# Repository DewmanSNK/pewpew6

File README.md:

# pewpew6
## Re-map and Rapid Fire
### Introduction

Based on buffi's original openpewpew, pewpew6 is an Arduino Nano based device for rapid fire and button remap in a JAMMA arcade cabinet. Pewpew6 supports up to 6 input buttons and can map those to any of 6 outputs. It simply connects in-line between the control panel buttons and the existing wiring harness. In an unconfigured state pewpew6 will provide simple passthrough, making it as though pewpew6 was not even installed. To load custom rapid fire and button remapping, pewpew6 leverages NFC cards. An NFC card card be configured with a desired auto fire and button remapping configuration. When the card is in proximity of the NFC reader, PewPew6 will change configuration on the fly and apply the rapid fire and remap settings stored on the card. This allows you to preconfigure you favorite buttons mappings and/or auto fire rates and store those on any number of NFC cards. 

### pewpew6 Features

- 6 button input and 6 outputs
- Button Remap
- Separate frames_on and frames_off rapid fire settings
- NFC card reader for loading settings
- 6 LED indicators show per button configuration

### NFC Card Format

Settings are stored in a 'Text Record' on the NFC card. 

Each line consists of the following comma separated values:  
(Button)(rapid enable)(frames_on)(frames_off)(Output)  

-Only one button definition per line  
-Last button definition ends with ';'  

Line Example
-------
A,0,1,1,1 = Button A, No auto fire enabled, 1 frame_on, 1 frame_off, Output 1  
**Note - When auto fire is disabled, the frame_on/frame_off vales are meaningless**  

Example Text Record 1:
--------------------
A,0,1,1,1  
B,0,1,1,2  
C,0,1,1,3  
D,0,1,1,4  
E,0,1,1,5  
F,0,1,1,6;  

The example text record 1 shown above displays the correct format. The settings in this example are the default settings stored in the Arduino.   
No rapid fire, no remapping - passthrough only.  

Example Text Record 2:
--------------------
A,0,1,1,1  
B,1,2,2,1  
C,1,1,4,1  
D,1,4,4,1  
E,1,10,1,1  
F,1,5,5,1;  

The example text record 2 shown above maps all 6 buttons to JAMMA-1  
Button A has no rapid fire, 1 frame_on, 1 frame_off, JAMMA-1  
Button B has rapid fire enabled, 1 frame_on, 1 frame_off, JAMMA-1  
Button C has rapid fire enabled, 1 frame_on, 4 frame_off, JAMMA-1  
Button D has rapid fire enabled, 4 frame_on, 4 frame_off, JAMMA-1  
Button E has rapid fire enabled, 10 frame_on, 1 frame_off, JAMMA-1  
Button F has rapid fire enabled, 5 frame_on, 5 frame_off, JAMMA-1  

Example Text Record 3:
--------------------
A,0,1,1,1  
B,0,2,2,2  
D,0,4,4,3  
E,0,10,10,4;  

The example text record 3 shown above is a fighting game example.  
Only 4 buttons are mapped, all buttons have rapid fire disabled - this is used only for button remapping and no rapid fire.

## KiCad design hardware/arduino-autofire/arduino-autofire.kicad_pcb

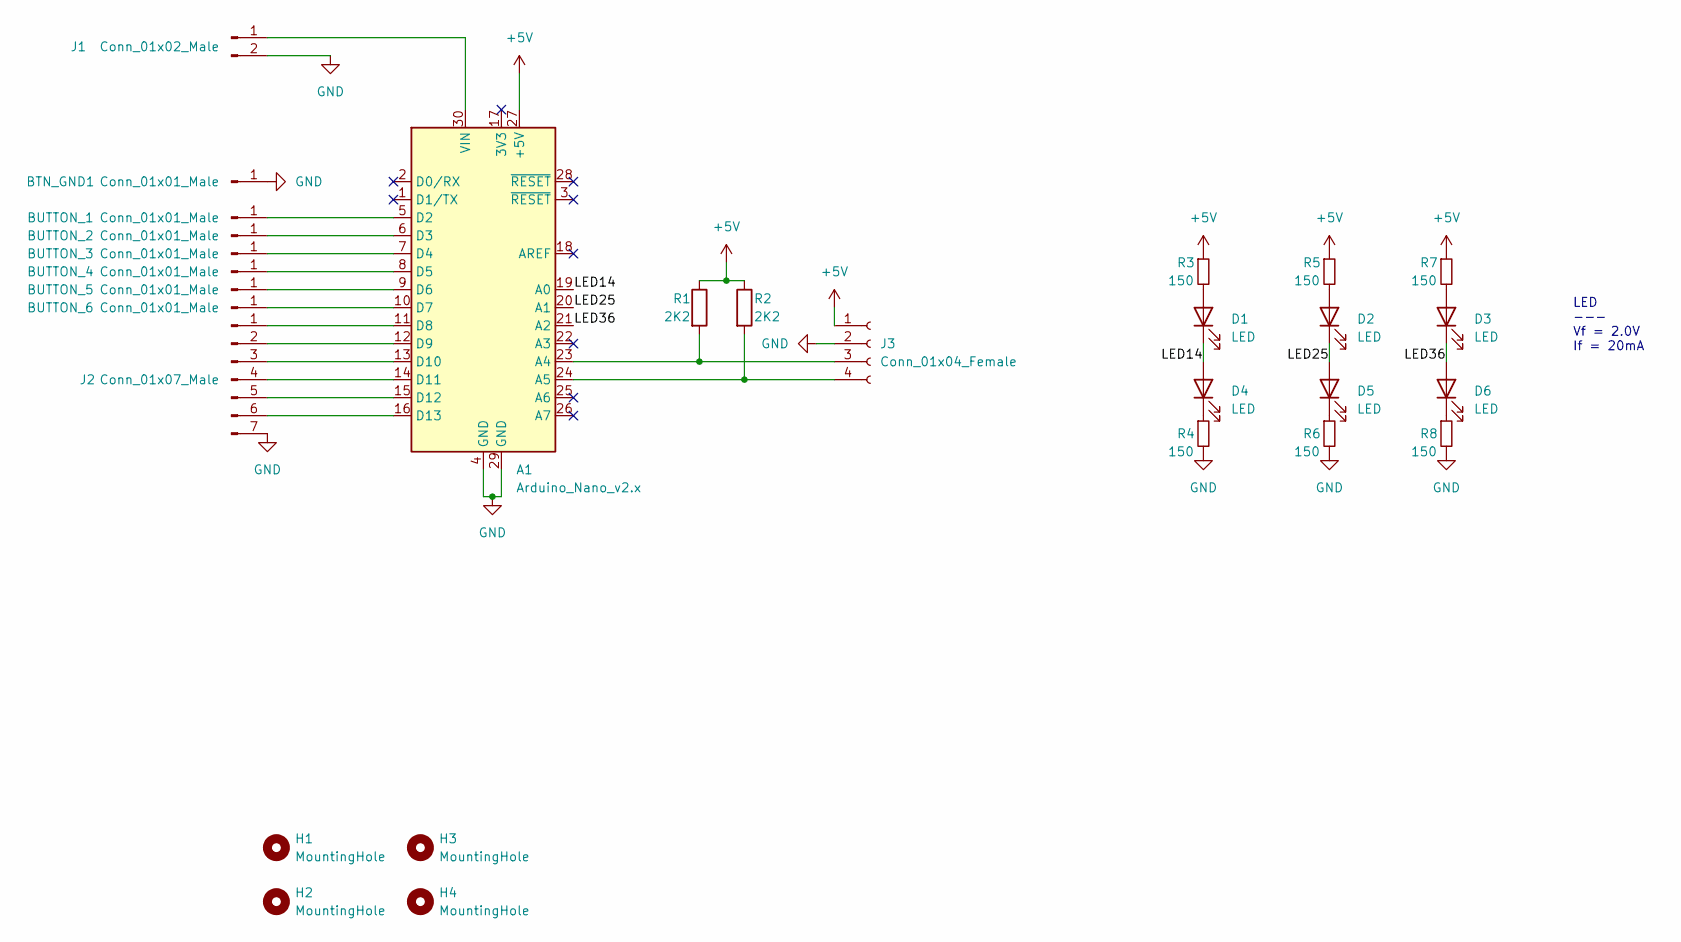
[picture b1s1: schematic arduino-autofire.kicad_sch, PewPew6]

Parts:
A1: Arduino_Nano_v2.x; Arduino_Nano_3D
BTN_GND1: Conn_01x01_Male; RA_Pin_D1.3mm_5.0mm
BUTTON_1, BUTTON_2, BUTTON_3, BUTTON_4, BUTTON_5, BUTTON_6: Conn_01x01_Male; RA_Pin_D1.3mm_5.0mm
D1, D2, D3, D4, D5, D6: LED; LED_0805_2012Metric_Pad1.15x1.40mm_HandSolder
H1, H2, H3, H4: MountingHole; MountingHole_3.2mm_M3
J1: Conn_01x02_Male; JST_EH_S2B-EH_1x02_P2.50mm_Horizontal
J2: Conn_01x07_Male; JST_EH_S7B-EH_1x07_P2.50mm_Horizontal
J3: Conn_01x04_Female; JST_EH_S4B-EH_1x04_P2.50mm_Horizontal
R1, R2: 2K2; R_0805_2012Metric_Pad1.20x1.40mm_HandSolder
R3, R4, R5, R6, R7, R8: 150; R_0805_2012Metric_Pad1.20x1.40mm_HandSolder

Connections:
+5V: A1.27 (+5V), J3.1, R1.1, R2.1, R3.1, R5.1, R7.1
/LED14: A1.19 (A0), D1.1 (K), D4.2 (A)
/LED25: A1.20 (A1), D2.1 (K), D5.2 (A)
/LED36: A1.21 (A2), D3.1 (K), D6.2 (A)
GND: A1.4 (GND), A1.29 (GND), BTN_GND1.1, J1.2, J2.7, J3.2, R4.2, R6.2, R8.2
unnamed: A1.5 (D2), BUTTON_1.1
unnamed: A1.6 (D3), BUTTON_2.1
unnamed: A1.7 (D4), BUTTON_3.1
unnamed: A1.8 (D5), BUTTON_4.1
unnamed: A1.9 (D6), BUTTON_5.1
unnamed: A1.10 (D7), BUTTON_6.1
unnamed: A1.11 (D8), J2.1
unnamed: A1.12 (D9), J2.2
unnamed: A1.13 (D10), J2.3
unnamed: A1.14 (D11), J2.4
unnamed: A1.15 (D12), J2.5
unnamed: A1.16 (D13), J2.6
unnamed: A1.23 (A4), J3.3, R1.2
unnamed: A1.24 (A5), J3.4, R2.2
unnamed: A1.30 (VIN), J1.1
unnamed: D1.2 (A), R3.2
unnamed: D2.2 (A), R5.2
unnamed: D3.2 (A), R7.2
unnamed: D4.1 (K), R4.1
unnamed: D5.1 (K), R6.1
unnamed: D6.1 (K), R8.1

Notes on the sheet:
LED --- Vf = 2.0V If = 20mA

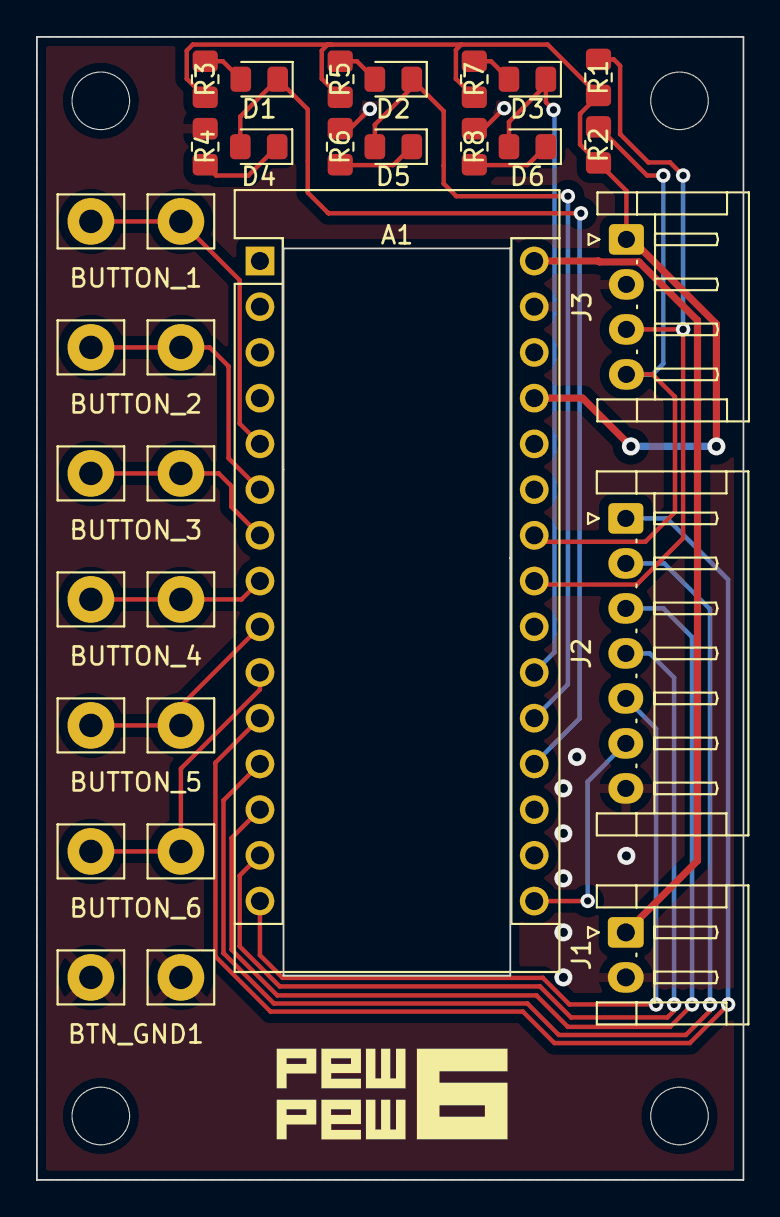
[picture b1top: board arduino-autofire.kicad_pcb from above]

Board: 2 copper layers, 39.2 x 63.5 mm, 29 parts (0 on the bottom side), 26 nets.

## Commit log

2022-06-03 Added logo and gerbers
